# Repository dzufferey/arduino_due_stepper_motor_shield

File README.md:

# Arduino Due Stepper Motors Shield

A shield for [g2](https://github.com/synthetos/g2) with 3 [TB67S249FTG](https://www.pololu.com/product/2973) motor drivers.

## Status

Not yet tested!

The pinout is not extactly the G2 pinout.
Here are the modifications:
* uses only 3 motors
  - motor 1
    * m1enab: 22
    * m1ms0:  24
    * m1ms1:  26
    * m1ms2:  28
  - motor 2
    * m2enab: 23
    * m2ms0:  25
    * m2ms1:  27
    * m2ms2:  29
  - motor 3
    * m3enab: 30
    * m3ms0:  32
    * m3ms1:  34
    * m3ms2:  36
* interlock: 51

## License and Attributions

* The Arduino Due componenent and footprint come from [Freetronics Pty Ltd](https://github.com/freetronics/freetronics_kicad_library) (CC-BY-SA) and [Nicholas C Lewis](https://www.thingiverse.com/thing:9630) (CC-BY).

This work is licensed under a [Creative Commons Attribution-ShareAlike 4.0 International License](https://creativecommons.org/licenses/by-sa/4.0/).

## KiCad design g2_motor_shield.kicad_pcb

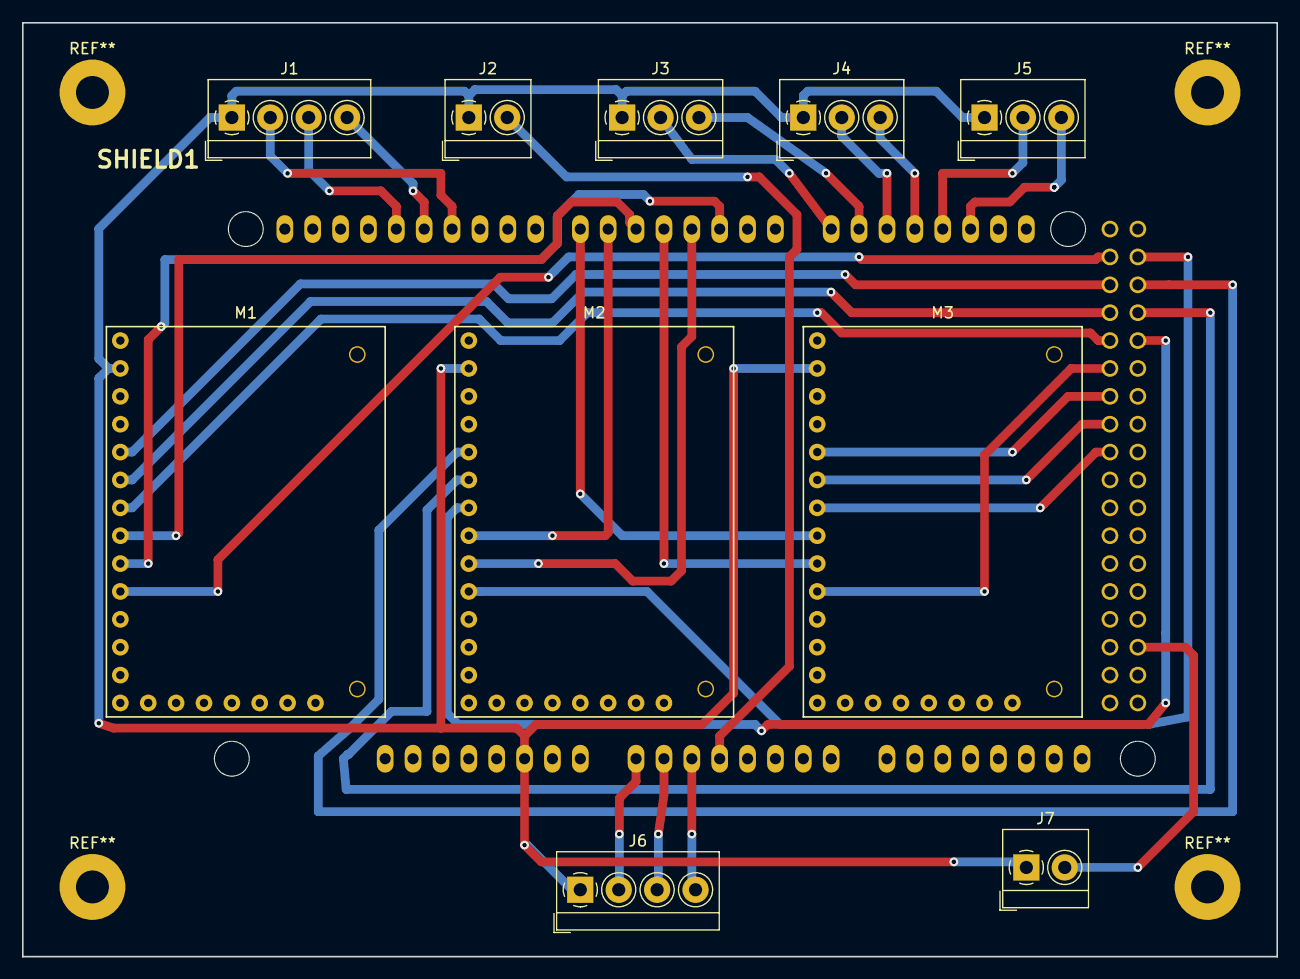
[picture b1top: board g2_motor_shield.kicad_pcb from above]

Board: 2 copper layers, 114.3 x 85.1 mm, 11 parts (0 on the bottom side), 33 nets.

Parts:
J1: Spindle; TerminalBlock_4Ucon_1x04_P3.50mm_Horizontal
J2: Cooling; TerminalBlock_4Ucon_1x02_P3.50mm_Horizontal
J3: X limits; TerminalBlock_4Ucon_1x03_P3.50mm_Horizontal
J4: Y limits; TerminalBlock_4Ucon_1x03_P3.50mm_Horizontal
J5: Z limits; TerminalBlock_4Ucon_1x03_P3.50mm_Horizontal
J6: Buttons; TerminalBlock_4Ucon_1x04_P3.50mm_Horizontal
J7: Interlock; TerminalBlock_4Ucon_1x02_P3.50mm_Horizontal
M1, M2, M3: TB67S249FTG; TB67S2x9FTG
SHIELD1: ARDUINO_DUE_SHIELD; ARDUINO_DUE_SHIELD_lite

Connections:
unnamed: J1.1, J2.1, J3.1, J4.1, J5.1, J6.1, J7.1, M1.2, M2.2, M3.2, SHIELD1.GND1
unnamed: J1.2, SHIELD1.11
unnamed: J1.3, SHIELD1.13
unnamed: J1.4, SHIELD1.12
unnamed: J2.2, SHIELD1.AD3
unnamed: J3.2, SHIELD1.14
unnamed: J3.3, SHIELD1.15
unnamed: J4.2, SHIELD1.16
unnamed: J4.3, SHIELD1.17
unnamed: J5.2, SHIELD1.18
unnamed: J5.3, SHIELD1.19
unnamed: J6.2, SHIELD1.AD0
unnamed: J6.3, SHIELD1.AD1
unnamed: J6.4, SHIELD1.AD2
unnamed: J7.2, SHIELD1.51
unnamed: M1.5, SHIELD1.24
unnamed: M1.6, SHIELD1.26
unnamed: M1.7, SHIELD1.28
unnamed: M1.8, SHIELD1.5
unnamed: M1.9, SHIELD1.2
unnamed: M1.10, SHIELD1.22
unnamed: M2.5, SHIELD1.25
unnamed: M2.6, SHIELD1.27
unnamed: M2.7, SHIELD1.29
unnamed: M2.8, SHIELD1.6
unnamed: M2.9, SHIELD1.3
unnamed: M2.10, SHIELD1.23
unnamed: M3.5, SHIELD1.32
unnamed: M3.6, SHIELD1.34
unnamed: M3.7, SHIELD1.36
unnamed: M3.8, SHIELD1.7
unnamed: M3.9, SHIELD1.4
unnamed: M3.10, SHIELD1.30

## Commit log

2019-04-28 first draft
2019-05-02 toward a prototype
